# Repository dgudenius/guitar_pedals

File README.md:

# guitar_pedals
Guitar Pedal schematics, layouts, and other build info

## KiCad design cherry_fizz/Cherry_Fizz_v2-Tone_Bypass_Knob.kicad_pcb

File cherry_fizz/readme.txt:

Big Muff Pi inspired fuzz circuit

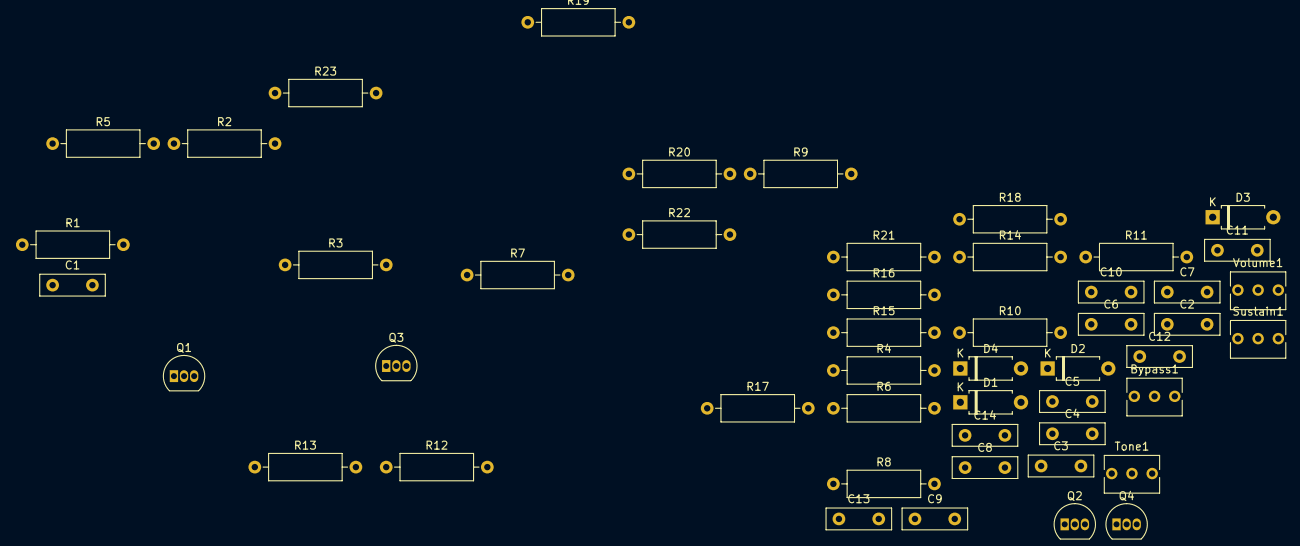
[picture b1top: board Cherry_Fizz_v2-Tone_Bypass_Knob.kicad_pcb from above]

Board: 2 copper layers, 49 parts (0 on the bottom side), 28 nets, no tracks yet.

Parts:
Bypass1: A250k; Potentiometer_Bourns_3266Y_Vertical
C1, C3, C4, C7, C12, C13: .1u; C_Disc_D8.0mm_W2.5mm_P5.00mm
C2, C6, C9: 470p; C_Disc_D8.0mm_W2.5mm_P5.00mm
C5, C8: .047u; C_Disc_D8.0mm_W2.5mm_P5.00mm
C10: .0047u; C_Disc_D8.0mm_W2.5mm_P5.00mm
C11: .01u; C_Disc_D8.0mm_W2.5mm_P5.00mm
C14: 1u; C_Disc_D8.0mm_W2.5mm_P5.00mm
D1: 1n914; D_A-405_P7.62mm_Horizontal
D2, D3, D4: 1N914; D_A-405_P7.62mm_Horizontal
Q1: BC337; TO-92_Inline
Q2, Q3: BC549; TO-92_Inline
Q4: BC547; TO-92_Inline
R1, R17: 39k; R_Axial_DIN0309_L9.0mm_D3.2mm_P12.70mm_Horizontal
R2, R8, R19: 470k; R_Axial_DIN0309_L9.0mm_D3.2mm_P12.70mm_Horizontal
R3, R9, R14, R20: 100k; R_Axial_DIN0309_L9.0mm_D3.2mm_P12.70mm_Horizontal
R4, R10, R15: 390; R_Axial_DIN0309_L9.0mm_D3.2mm_P12.70mm_Horizontal
R5, R7, R11, R12, R16, R22: 10k; R_Axial_DIN0309_L9.0mm_D3.2mm_P12.70mm_Horizontal
R6: 1k; R_Axial_DIN0309_L9.0mm_D3.2mm_P12.70mm_Horizontal
R13: 470K; R_Axial_DIN0309_L9.0mm_D3.2mm_P12.70mm_Horizontal
R18: 22k; R_Axial_DIN0309_L9.0mm_D3.2mm_P12.70mm_Horizontal
R21: 2.2K; R_Axial_DIN0309_L9.0mm_D3.2mm_P12.70mm_Horizontal
R23: 1.2M; R_Axial_DIN0309_L9.0mm_D3.2mm_P12.70mm_Horizontal
Sustain1: A50k; Potentiometer_Bourns_3266Y_Vertical
Tone1: B100k; Potentiometer_Bourns_3266Y_Vertical
Volume1: A100k; Potentiometer_Bourns_3266Y_Vertical

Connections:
GND: C11.2, R3.2, R4.2, R6.2, R9.2, R10.2, R14.2, R15.2, R18.1, R20.2, R21.2, R23.2, Volume1.3
In: R1.2, R23.1
unnamed: Bypass1.1, Bypass1.2, C9.1, C10.2, D3.1, D4.2, Q3.1, R13.1, R16.2, R17.2
unnamed: Bypass1.3, C12.2, Tone1.2
unnamed: C1.1, C2.2, Q1.2, R2.2, R3.1
unnamed: C1.2, R1.1
unnamed: C2.1, C3.2, Q1.1, R2.1, R5.2
unnamed: C3.1, Sustain1.1
unnamed: C4.1, R7.2
unnamed: C4.2, Sustain1.2
unnamed: C5.1, D1.2, D2.1
unnamed: C5.2, C6.2, Q2.2, R7.1, R8.2, R9.1
unnamed: C6.1, C7.2, D1.1, D2.2, Q2.1, R8.1, R11.2
unnamed: C7.1, R12.2
unnamed: C8.1, D3.2, D4.1
unnamed: C8.2, C9.2, Q3.2, R12.1, R13.2, R14.1
unnamed: C10.1, R18.2, Tone1.1
unnamed: C11.1, R17.1, Tone1.3
unnamed: C12.1, Q4.2, R19.2, R20.1
unnamed: C13.1, Volume1.1
unnamed: C13.2, Q4.1, R19.1, R22.2
unnamed: C14.2, Volume1.2
unnamed: Q1.3, R4.1
unnamed: Q2.3, R10.1
unnamed: Q3.3, R15.1
unnamed: Q4.3, R21.1
unnamed: R6.1, Sustain1.3
V+: R5.1, R11.1, R16.1, R22.1

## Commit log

2021-04-24 Create blank
